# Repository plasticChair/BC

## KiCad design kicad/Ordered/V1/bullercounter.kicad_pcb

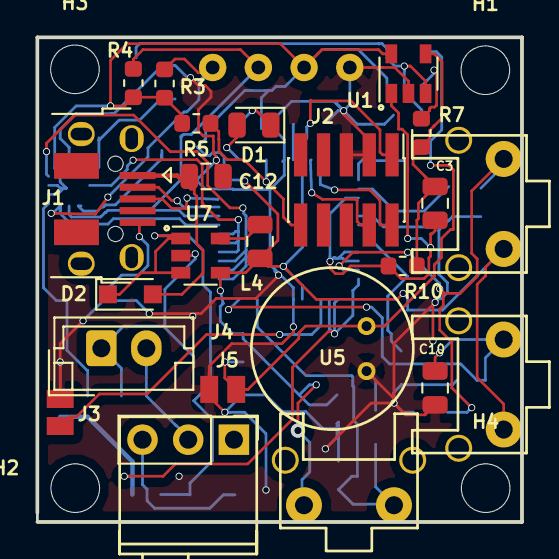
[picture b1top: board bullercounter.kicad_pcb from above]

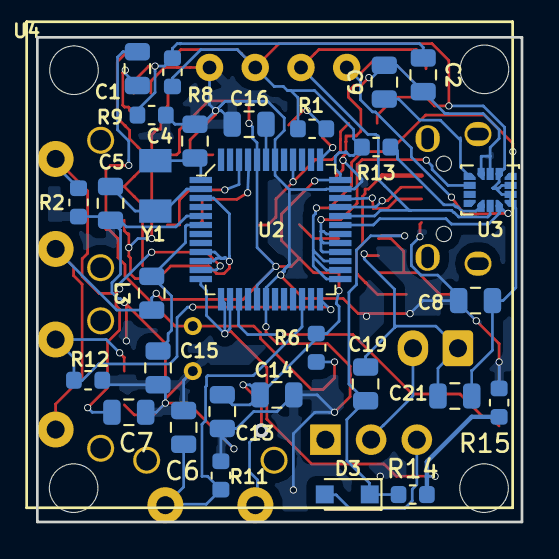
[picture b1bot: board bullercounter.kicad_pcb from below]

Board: 2 copper layers, 26.9 x 26.9 mm, 57 parts (30 on the bottom side), 35 nets.

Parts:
C1: 4.7uF; C_0805_2012Metric
C2: 1uF; C_0805_2012Metric
C3, C6, C7, C10: 100pF; C_0805_2012Metric
C4, C5, C21: C; C_0805_2012Metric
C8, C9, C12: 100nF; C_0805_2012Metric
C13, C14, C15, C16: 82n; C_0805_2012Metric
C19: 0.1uF; C_0805_2012Metric
D1: LED_B; LED_0805_2012Metric
D2, D3: D_Schottky; D_SOD-323_HandSoldering
H1, H2, H3, H4: MountingHole; MountingHole_2.7mm
J1: USB_B_Micro; USB_Micro-B_Adafruit
J2: Conn_ARM_JTAG_SWD_10; PinHeader_2x05_P1.27mm_Vertical_SMD
J3: Serial; SMD_1Pin_1.5mm
J4: Conn_01x02_Female; JST_EH_B02B-EH-A_1x02_P2.50mm_Vertical
J5: TP; SMD_1Pin_1.5mm
L3, L4: INDUCTOR; L_0805_2012Metric
R1: 5.6; R_0603_1608Metric
R2, R5, R6, R8, R9, R11, R12, R13, R14, R15: 10k; R_0603_1608Metric
R3, R4: R; R_0603_1608Metric
R7: 1.5k; R_0603_1608Metric
R10: 100k; R_0603_1608Metric
SW1: SW_SPDT; Slide_Switch_RA_09.10290.01
SW3, SW4, SW5: Switch; ebay_RA_Mom_switch
U1: MCP6421; SOT-23-5
U2: ATSAMD21G18A-AUT; TQFP-48_7x7mm
U3: LSM6DS3; LGA-14_3x2.5mm_P0.5mm_LayoutBorder3x4y
U4: OLED_0.96_128x64
U5: MO043803_4.5mm
U7: LM3671; SOT-23-5
Y1: Crystal; TFE322P32K7680R

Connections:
/BatteryManagement/Batt-: C19.2, C21.2, J4.1, U7.2
/BatteryManagement/Batt_int: J4.2, SW1.2
/RESET: J2.10, R5.1, U2.40
/SWDCLK: J2.4, U2.45
/SWDIO: J2.2, U2.46
/USB_DM: J1.2, U2.33
/USB_DP: J1.3, U2.34
/VDDANA: C15.1, L3.2, U2.6
/VDDCORE: C16.1, U2.43
Audio_out: C3.1, R10.2, U1.1, U2.3, U2.9, U2.10
BattADC: R14.2, R15.2, U2.12, U2.13, U2.14
BattPwr: C19.1, D2.1, D3.1, R14.1, U7.1, U7.3
BattRtn: C2.2, C4.1, C5.1, C6.1, C7.1, C8.2, C9.2, C10.1, C12.1, C13.2, C14.2, C15.2, C16.2, J1.5, J2.3, J2.5, J3.1, J5.1, R2.2, R9.1, R11.2, R12.2, R15.1, U1.2, U2.5, U2.18, U2.35, U2.42, U3.6, U3.7, U4.1, U5.2
Fun_Btn_1: C7.2, R2.1, SW3.2, U2.11
Fun_Btn_2: C6.2, R11.1, SW4.2, U2.22
Fun_Btn_3: C10.2, R12.1, SW5.2, U2.24
IMU_INT: U2.28, U2.29, U2.30, U3.9
IMU_INT2: U2.25, U2.26, U2.27, U3.4
LED1_P2: D1.2, U2.37
unnamed: C1.1, R7.2
unnamed: C1.2, J5.2, R6.1, U5.1
unnamed: C2.1, R8.1, R9.2, U1.3
unnamed: C3.2, R7.1, R10.1, U1.4
unnamed: C4.2, U2.1, Y1.1
unnamed: C5.2, U2.2, Y1.2
unnamed: C9.1, U3.8
unnamed: D1.1, R1.1
unnamed: D3.2, SW1.3
unnamed: J3.2, U2.15
unnamed: L4.1, U7.5
unnamed: R13.1, U3.12
SCL: R4.2, U2.32, U3.13, U4.3
SDA: R3.2, U2.31, U3.14, U4.4
USB_PWR: C12.2, D2.2, J1.1
Vdd: C8.1, C13.1, C14.1, C21.1, J2.1, L3.1, L4.2, R1.2, R3.1, R4.1, R5.2, R6.2, R8.2, R13.2, SW3.1, SW4.1, SW5.1, U1.5, U2.17, U2.36, U2.44, U3.1, U3.2, U3.3, U3.5, U4.2, U7.4

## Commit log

2019-05-16 git init
2019-06-30 code updates
